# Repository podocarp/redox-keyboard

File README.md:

## Changes

This is a fork of the original. Additions:
- Added v1 version that uses low profile Kailh choc hot swap sockets compatible
  with both v1 and v2 switches
- Added v1 version that uses Kailh MX hot swap sockets

<h3 align="center">The Redox project repository</h3>

<div align="center">

</div>

---

The Redox project is an open-source, [QMK (Quantum Mechanical Keyboard Firmware)](https://github.com/qmk/qmk_firmware) powered, ergonomic split mechanical keyboard. This repository will be used to share information about the project and instruction on how to use and assemble the Redox keyboard.

**Designer's bio**: [Mattia Dal Ben (aka u/TiaMaT102)](mailto:matthewdibi@gmail.com) obtained a master's degree in Electrical Engineering with a specialization in Computer Science at the University of Udine. Currently works as a Software Engineer in R&D department for a big IoT and Embedded Computers company. Mechanical keyboard enthusiast and maker, the Redox keyboard is the result of all of his passions.

## Rationale

The Redox is a keyboard project designed with ergonomics in mind. It uses Cherry MX style mechanical switches laid out in a 7x5 columnar stagger layout with components that can easily be sourced.

The design was heavily inspired by the [Ergodox keyboard](https://www.ergodox.io/), and its main goal is to reduce the size without sacrificing too many keys, hence the name **Re**duced Ergo**dox**.

As an Ergodox user I couldn't ignore the few flaws of the original design and in a moment of arrogance I tried to fix them, thus the Redox features:
- Easier to reach thumb cluster.
- Additional easy-to-reach rotated 1.25u thumb key.
- Reduced size.
- Reduced costs (the Redox uses Arduino Pro Micro instead of the Teensy 2.0).
- Either half can be plugged in to the PC since each half can act as the master.
- Either half can work as a standalone keyboard to be used as a macropad/gaming keyboard.
- RGB backlighting support.
- 3D-printer friendly case.
- Wireless [see section below](#wireless-implementations)
- [VIA](https://caniusevia.com/) compatible (thanks to [Harshit Goel](https://github.com/harshitgoel96))
- [ZMK firmware](https://zmk.dev/) compatible (thanks to [toddmok](https://github.com/toddmok))
- [KMK firmware](http://kmkfw.io/) compatible

## Related Projects

- [**Redox handwire**](https://www.thingiverse.com/thing:2704567): The first incarnation of the Redox keyboard. It consists of a 3D-printed case and a handwired matrix.
  - [Tilted Redox case](https://www.thingiverse.com/thing:2767216): tilted case for the Redox prototype by jschloer.
    - [Tilted redox case pro micro](https://www.printables.com/model/382413-tilted-redox-case-for-micro-and-usbc): Remix of the tilted case to support pro micro and usb c instead of TRRS. 

  - [couscous-kbd](https://gitlab.com/cschalkwijk/couscous-kbd): Redox-inspired parametric OpenSCAD keyboard design.
  - [Redox tenting kit](https://www.thingiverse.com/make:484843): modified base to support tenting, mini-USB for the interconnect, and a hole for microswitch for reset needed when uploading new firmware by [Lenbok](https://github.com/Lenbok).
  - [Iris-inspired Redox case](https://github.com/Lenbok/scad-redox-case): a case inspired both by the Redox rev1.0 and the Iris designed with OpenSCAD by [Lenbok](https://github.com/Lenbok).
  - [Redodactyl keyboard](https://www.reddit.com/r/MechanicalKeyboards/comments/9j5pw5/enter_the_redodactyl_first_build/): handwired 3D printed Dactyl-inspired Redox variant by u/darknao.
- [**Redox Manuform**](https://www.thingiverse.com/thing:3503380): full rework of the Redox case inspired by the Dactyl Manuform. Designed by [Fosk\_LL](https://www.thingiverse.com/Fosk_LL/about).
- [**Redox rev1.0**](https://github.com/mattdibi/redox-keyboard/tree/master/redox): the Redox rev 1.0 is the first commercially available version of the Redox keyboard.
	- Rev1.0 PCBs: available at [Falbatech's store](https://falba.tech/product/redox-pcb-electrical-boards-set-of-2/)
    - Firmware sources:
        - [QMK firmware for Redox](https://github.com/mattdibi/qmk_firmware/tree/master/keyboards/redox)
        - [KMK firmware for Redox](https://github.com/KMKfw/kmk_firmware/tree/master/boards/redox)
	- 3D-printable cases:
        - [3D printable case](https://www.thingiverse.com/thing:2886662), freely available.
        - [Redox keyboard case (high profile)](https://www.thingiverse.com/thing:3825752), by [Michele Ferri](https://www.thingiverse.com/sako83/about).
        - [Travel-friendly Redox Keyboard case](https://www.thingiverse.com/thing:3607303), by [Fosk\_LL](https://www.thingiverse.com/Fosk_LL/about).
        - [Redox Neodox case](https://github.com/Pastitas/Redox-neodox-Case), by [Pastitas](https://github.com/Pastitas)
        - [Redox big battery](https://github.com/marco-silvestri/redox-big-battery), by [Marco Silvestri](https://github.com/marco-silvestri).
	- Commercially available cases:
		- [Falbatech's bamboo cases with tilt kit](https://falba.tech/product/redox-standard-lift-bamboo-wood-case-with-oil-finish/)
		- [Falbatech's fullhand bamboo cases](https://falba.tech/product/redox-fullhand-bamboo-wood-case-with-oil-finish-ver-2/)
- [**Redox rev1.0W**](https://github.com/mattdibi/redox-keyboard/tree/master/redox-w): the Redox rev 1.0W is the wireless version of the Redox keyboard.
    - Rev1.0W PCBs: gerbers available in [this repo](https://github.com/mattdibi/redox-keyboard/tree/master/redox-w/rev1.0W).
    - Falbatech's Rev1.0W Hot-swap PCBs: available at [Falbatech's store](https://falba.tech/product/redox-wireless-pcb-electrical-boards-set-of-2/) (Incompatible with the 3D-printable cases down below)
    - Firmware sources:
        - [QMK firmware for Redox wireless](https://github.com/mattdibi/qmk_firmware/tree/master/keyboards/redox_w)
        - [Nordic MCUs firmware for Redox wireless](https://github.com/mattdibi/redox-w-firmware)
	- 3D-printable cases:
        - [3D printed case](https://github.com/mattdibi/redox-keyboard/tree/master/redox-w/case), freely available.
        - [Redox Neodox case](https://github.com/Pastitas/Redox-neodox-Case), by [Pastitas](https://github.com/Pastitas)
    - Commercially available cases (only compatible with the Falbatech's store PCBs):
        - [Falbatech's bamboo and aliminium cases](https://falba.tech/product/redox-wireless-standard-lift-bamboo-wood-case-with-oil-finish/)
		- [Falbatech's fullhand bamboo cases](https://falba.tech/product/redox-wireless-standard-lift-bamboo-wood-case-with-oil-finish-ver-1/)
- [**Redox rev2.0WHS**](https://github.com/mattdibi/redox-keyboard/tree/master/redox-w): the Redox rev 2.0WHS is the wireless hot-swappable version of the Redox keyboard.
    - Rev2.0WHS PCBs: gerber files available [here](https://github.com/mattdibi/redox-keyboard/tree/master/redox-w/rev2.0WHS/pcb)
    - Firmware sources:
        - [QMK firmware for Redox wireless](https://github.com/mattdibi/qmk_firmware/tree/master/keyboards/redox_w)
        - [Nordic MCUs firmware for Redox wireless](https://github.com/mattdibi/redox-w-firmware)
	- 3D-printable case:
        - [3D printed case](https://github.com/mattdibi/redox-keyboard/tree/master/redox-w/rev2.0WHS/case), freely available.

## Wireless Implementations

The Redox keyboard uses three different wireless implementations, differentiated by firmware:
 - *QMK based*: Leveraging the [Gazel protocol](https://developer.nordicsemi.com/nRF5_SDK/nRF51_SDK_v5.x.x/doc/5.2.0/html/a00140.html). It needs its own PCB and a receiver dongle (see [Redox Wireless](https://github.com/mattdibi/redox-keyboard/tree/docs/zmk_update/redox-w) for details) and needs three YJ-14015 MCUs + a Pro Micro compatible controller.
 - *ZMK based*: Leveraging the Bluetooth protocol. It is based on the [Redox wired PCB](https://github.com/mattdibi/redox-keyboard/tree/master/redox) and the [nice!nano](https://nicekeyboards.com/nice-nano/) controller.
 - *KMK based*: Adding [Bluetooth Split](http://kmkfw.io/docs/split_keyboards#bluetooth-split-aka-no-trrs-currently-in-testing) code to `boards/redox/main.py`. Combined with a [compatible](http://kmkfw.io/docs/Officially_Supported_Microcontrollers) wireless controller completes wireless configuration. Would advice adding [Bluetooth keycodes](http://kmkfw.io/docs/keycodes#bluetooth-keys) in keymap; `keyboard.keymap` element in `main.py`.

 The notable differences for the three implementations are as follows:
 - _Battery life_: QMK Redox Wireless uses two CR2032 coin cell batteries which last [approximately one year (YMMV)](https://github.com/mattdibi/redox-keyboard/tree/master/redox-w#battery-usage), while the nice!nano support LiPo rechargable batteries (you can choose the capacity you want but expect them to last for a [few weeks on a single charge](https://zmk.dev/power-profiler)).
 - _Flexibility_: The receiver dongle limits the flexibility of QMK Redox Wireless.
 - _Cost_: The 3x YJ-14015 + Pro Micro combo is cheaper than two wireless controllers required for ZMK and wireless KMK.
 - _Range_: Bluetooth implementations, of ZMK and KMK, should be more capable than what can be achieved with the QMK Redox Wireless (At this point in time, I lack the evidence to support these claims though).

## Physical Key Layout

### Keycaps

| Size  | Qty |                                     Notes                                    |
|-------|:---:|:----------------------------------------------------------------------------:|
| 1.5u  |   6 |                                                                              |
| 1.25u |  10 | You can get away with 8 if you use two 1u keycaps for the 1.25u rotated keys |
| 1u    |  54 |                                                                              |

> :information_source: On [pimpmykeyboard.com](https://pimpmykeyboard.com/sa-1976-keyset-two-shot/) site you can find a SA 1976 keyset kit specifically made for the Redox keyboard: the "Ergo Redox kit (12 keys)".

## Affiliations

In partnership with Falbatech you can now use the code "**mattdibi05**" on Falbatech's store for a 5% OFF special discount.

## Donations

If you've read this far and found something useful, please consider donating to help me maintain and further develop this project.

<p align="center">

</p>

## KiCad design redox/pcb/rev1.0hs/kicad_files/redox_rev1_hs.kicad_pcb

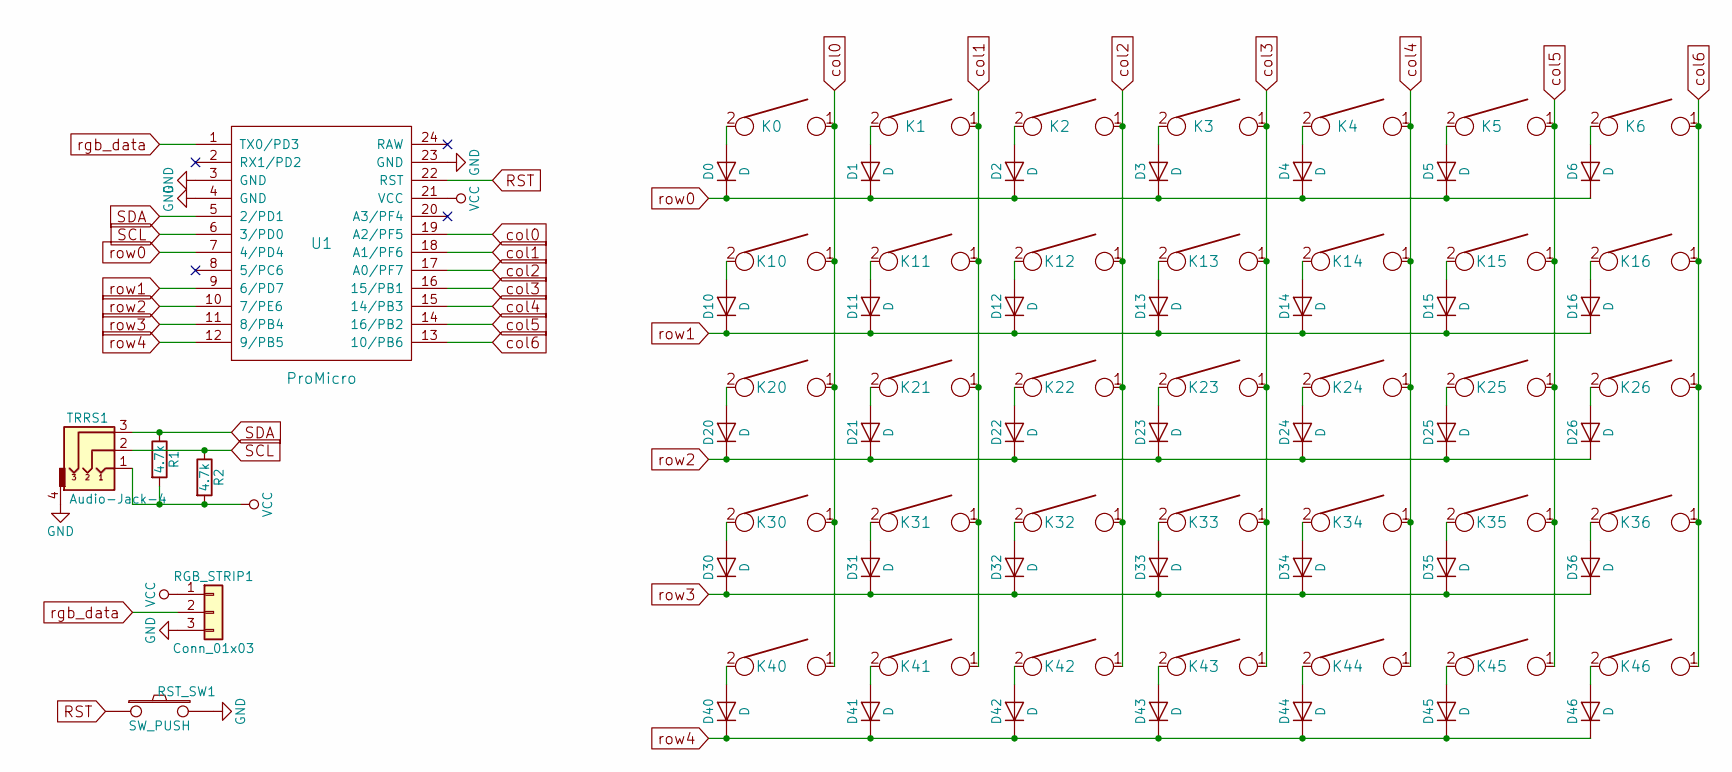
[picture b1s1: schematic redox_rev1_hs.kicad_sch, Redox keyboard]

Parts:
D0, D1, D2, D3, D4, D5, D6, D10, D11, D12, D13, D14, D15, D16, D20, D21, D22, D23, D24, D25, D26, D30, D31, D32, D33, D34, D35, D36, D40, D41, D42, D43, D44, D45, D46: D; Diode-dual
K0, K10, K20, K30, K44: KEYSW; SW_Hotswap_Kailh_MX_1.25u
K1, K2, K3, K4, K5, K6, K11, K12, K13, K14, K15, K21, K22, K23, K24, K25, K26, K31, K32, K33, K34, K35, K36, K40, K41, K42, K43: KEYSW; SW_Hotswap_Kailh_MX_1.00u
K16, K45, K46: KEYSW; SW_Hotswap_Kailh_MX_1.50u
R1, R2: 4.7k; Resistor-Compact
RGB_STRIP1: Conn_01x03; Pin_Header_Straight_1x03_Pitch2.54mm
RST_SW1: SW_PUSH; SW_PUSH_6mm_h4.3mm
TRRS1: Audio-Jack-4; TRRS-PJ-320A-dual
U1: ProMicro; ArduinoProMicro

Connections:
GND: RGB_STRIP1.3, RST_SW1.2, TRRS1.4, U1.3 (GND), U1.4 (GND), U1.23 (GND)
unnamed: D0.2 (A), K0.2
unnamed: D1.2 (A), K1.2
unnamed: D2.2 (A), K2.2
unnamed: D3.2 (A), K3.2
unnamed: D4.2 (A), K4.2
unnamed: D5.2 (A), K5.2
unnamed: D6.2 (A), K6.2
unnamed: D10.2 (A), K10.2
unnamed: D11.2 (A), K11.2
unnamed: D12.2 (A), K12.2
unnamed: D13.2 (A), K13.2
unnamed: D14.2 (A), K14.2
unnamed: D15.2 (A), K15.2
unnamed: D16.2 (A), K16.2
unnamed: D20.2 (A), K20.2
unnamed: D21.2 (A), K21.2
unnamed: D22.2 (A), K22.2
unnamed: D23.2 (A), K23.2
unnamed: D24.2 (A), K24.2
unnamed: D25.2 (A), K25.2
unnamed: D26.2 (A), K26.2
unnamed: D30.2 (A), K30.2
unnamed: D31.2 (A), K31.2
unnamed: D32.2 (A), K32.2
unnamed: D33.2 (A), K33.2
unnamed: D34.2 (A), K34.2
unnamed: D35.2 (A), K35.2
unnamed: D36.2 (A), K36.2
unnamed: D40.2 (A), K40.2
unnamed: D41.2 (A), K41.2
unnamed: D42.2 (A), K42.2
unnamed: D43.2 (A), K43.2
unnamed: D44.2 (A), K44.2
unnamed: D45.2 (A), K45.2
unnamed: D46.2 (A), K46.2
RST: RST_SW1.1, U1.22 (RST)
SCL: R2.1, TRRS1.2, U1.6 (3/PD0)
SDA: R1.1, TRRS1.3, U1.5 (2/PD1)
VCC: R1.2, R2.2, RGB_STRIP1.1, TRRS1.1, U1.21 (VCC)
col0: K0.1, K10.1, K20.1, K30.1, K40.1, U1.19 (A2/PF5)
col1: K1.1, K11.1, K21.1, K31.1, K41.1, U1.18 (A1/PF6)
col2: K2.1, K12.1, K22.1, K32.1, K42.1, U1.17 (A0/PF7)
col3: K3.1, K13.1, K23.1, K33.1, K43.1, U1.16 (15/PB1)
col4: K4.1, K14.1, K24.1, K34.1, K44.1, U1.15 (14/PB3)
col5: K5.1, K15.1, K25.1, K35.1, K45.1, U1.14 (16/PB2)
col6: K6.1, K16.1, K26.1, K36.1, K46.1, U1.13 (10/PB6)
rgb_data: RGB_STRIP1.2, U1.1 (TX0/PD3)
row0: D0.1 (K), D1.1 (K), D2.1 (K), D3.1 (K), D4.1 (K), D5.1 (K), D6.1 (K), U1.7 (4/PD4)
row1: D10.1 (K), D11.1 (K), D12.1 (K), D13.1 (K), D14.1 (K), D15.1 (K), D16.1 (K), U1.9 (6/PD7)
row2: D20.1 (K), D21.1 (K), D22.1 (K), D23.1 (K), D24.1 (K), D25.1 (K), D26.1 (K), U1.10 (7/PE6)
row3: D30.1 (K), D31.1 (K), D32.1 (K), D33.1 (K), D34.1 (K), D35.1 (K), D36.1 (K), U1.11 (8/PB4)
row4: D40.1 (K), D41.1 (K), D42.1 (K), D43.1 (K), D44.1 (K), D45.1 (K), D46.1 (K), U1.12 (9/PB5)

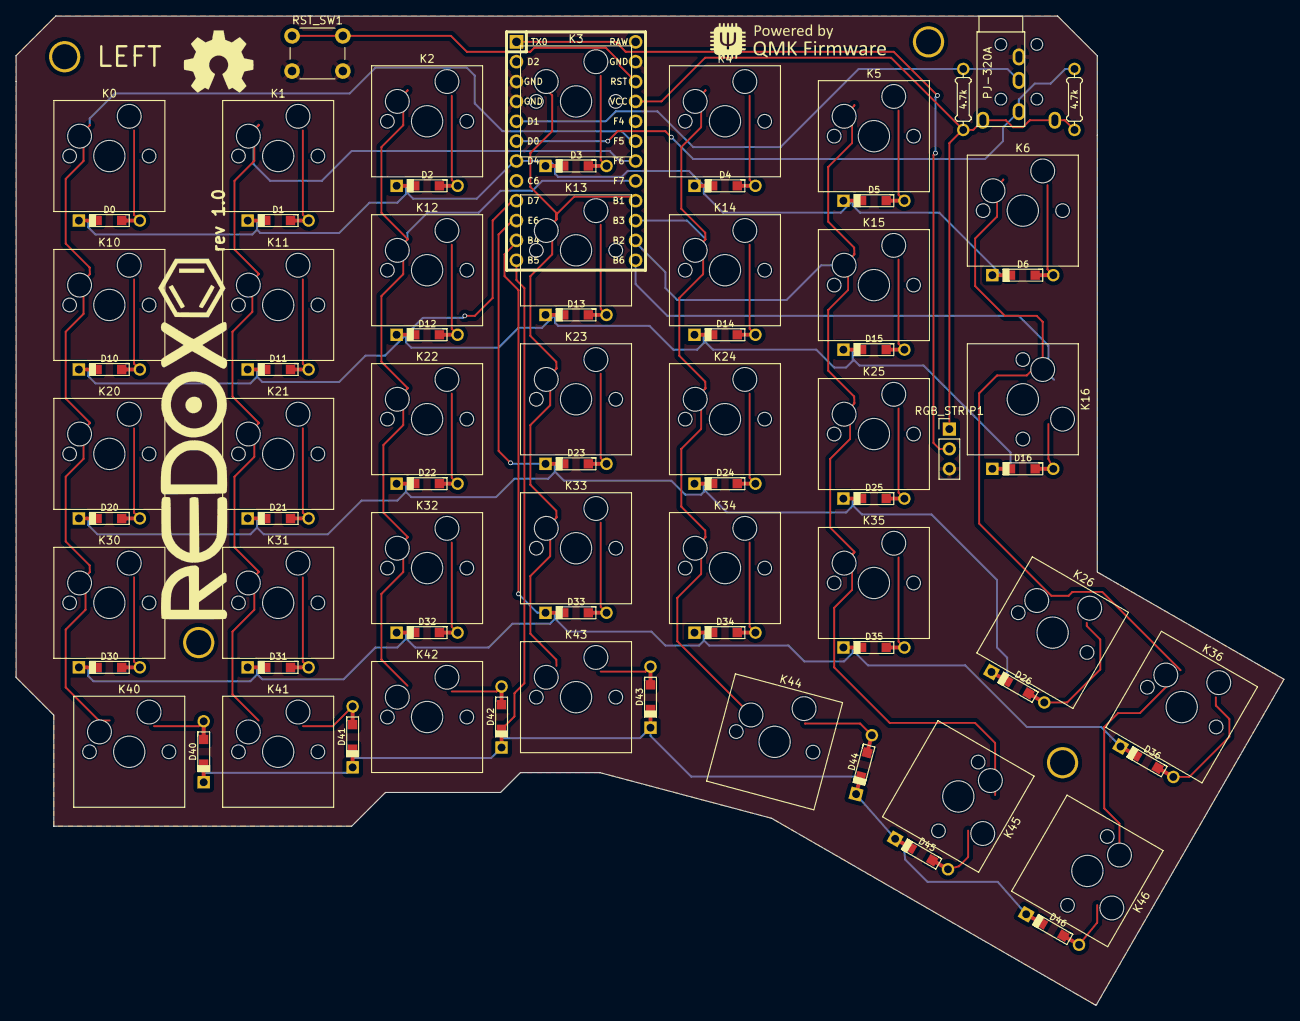
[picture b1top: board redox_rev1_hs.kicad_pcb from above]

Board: 2 copper layers, 162.2 x 126.5 mm, 80 parts (0 on the bottom side), 53 nets.

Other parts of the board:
HOLE_M3, HOLE_M3#2, HOLE_M3#3, HOLE_M3#4: VAL**; HOLE_M3

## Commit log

2023-11-21 change to kailh choc hotswap sockets
2023-11-23 move lp to new folder, restore old one
2023-11-23 move switch footprints into local folder and change schematic to use them instead
2023-11-23 add files

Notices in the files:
README.md:
License: MIT
